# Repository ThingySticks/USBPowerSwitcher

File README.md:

# USB Power Controller

TODO: Write Readme.md

See: https://www.hackster.io/TinamousSteve/alexa-enabled-usb-power-switch-93bab3

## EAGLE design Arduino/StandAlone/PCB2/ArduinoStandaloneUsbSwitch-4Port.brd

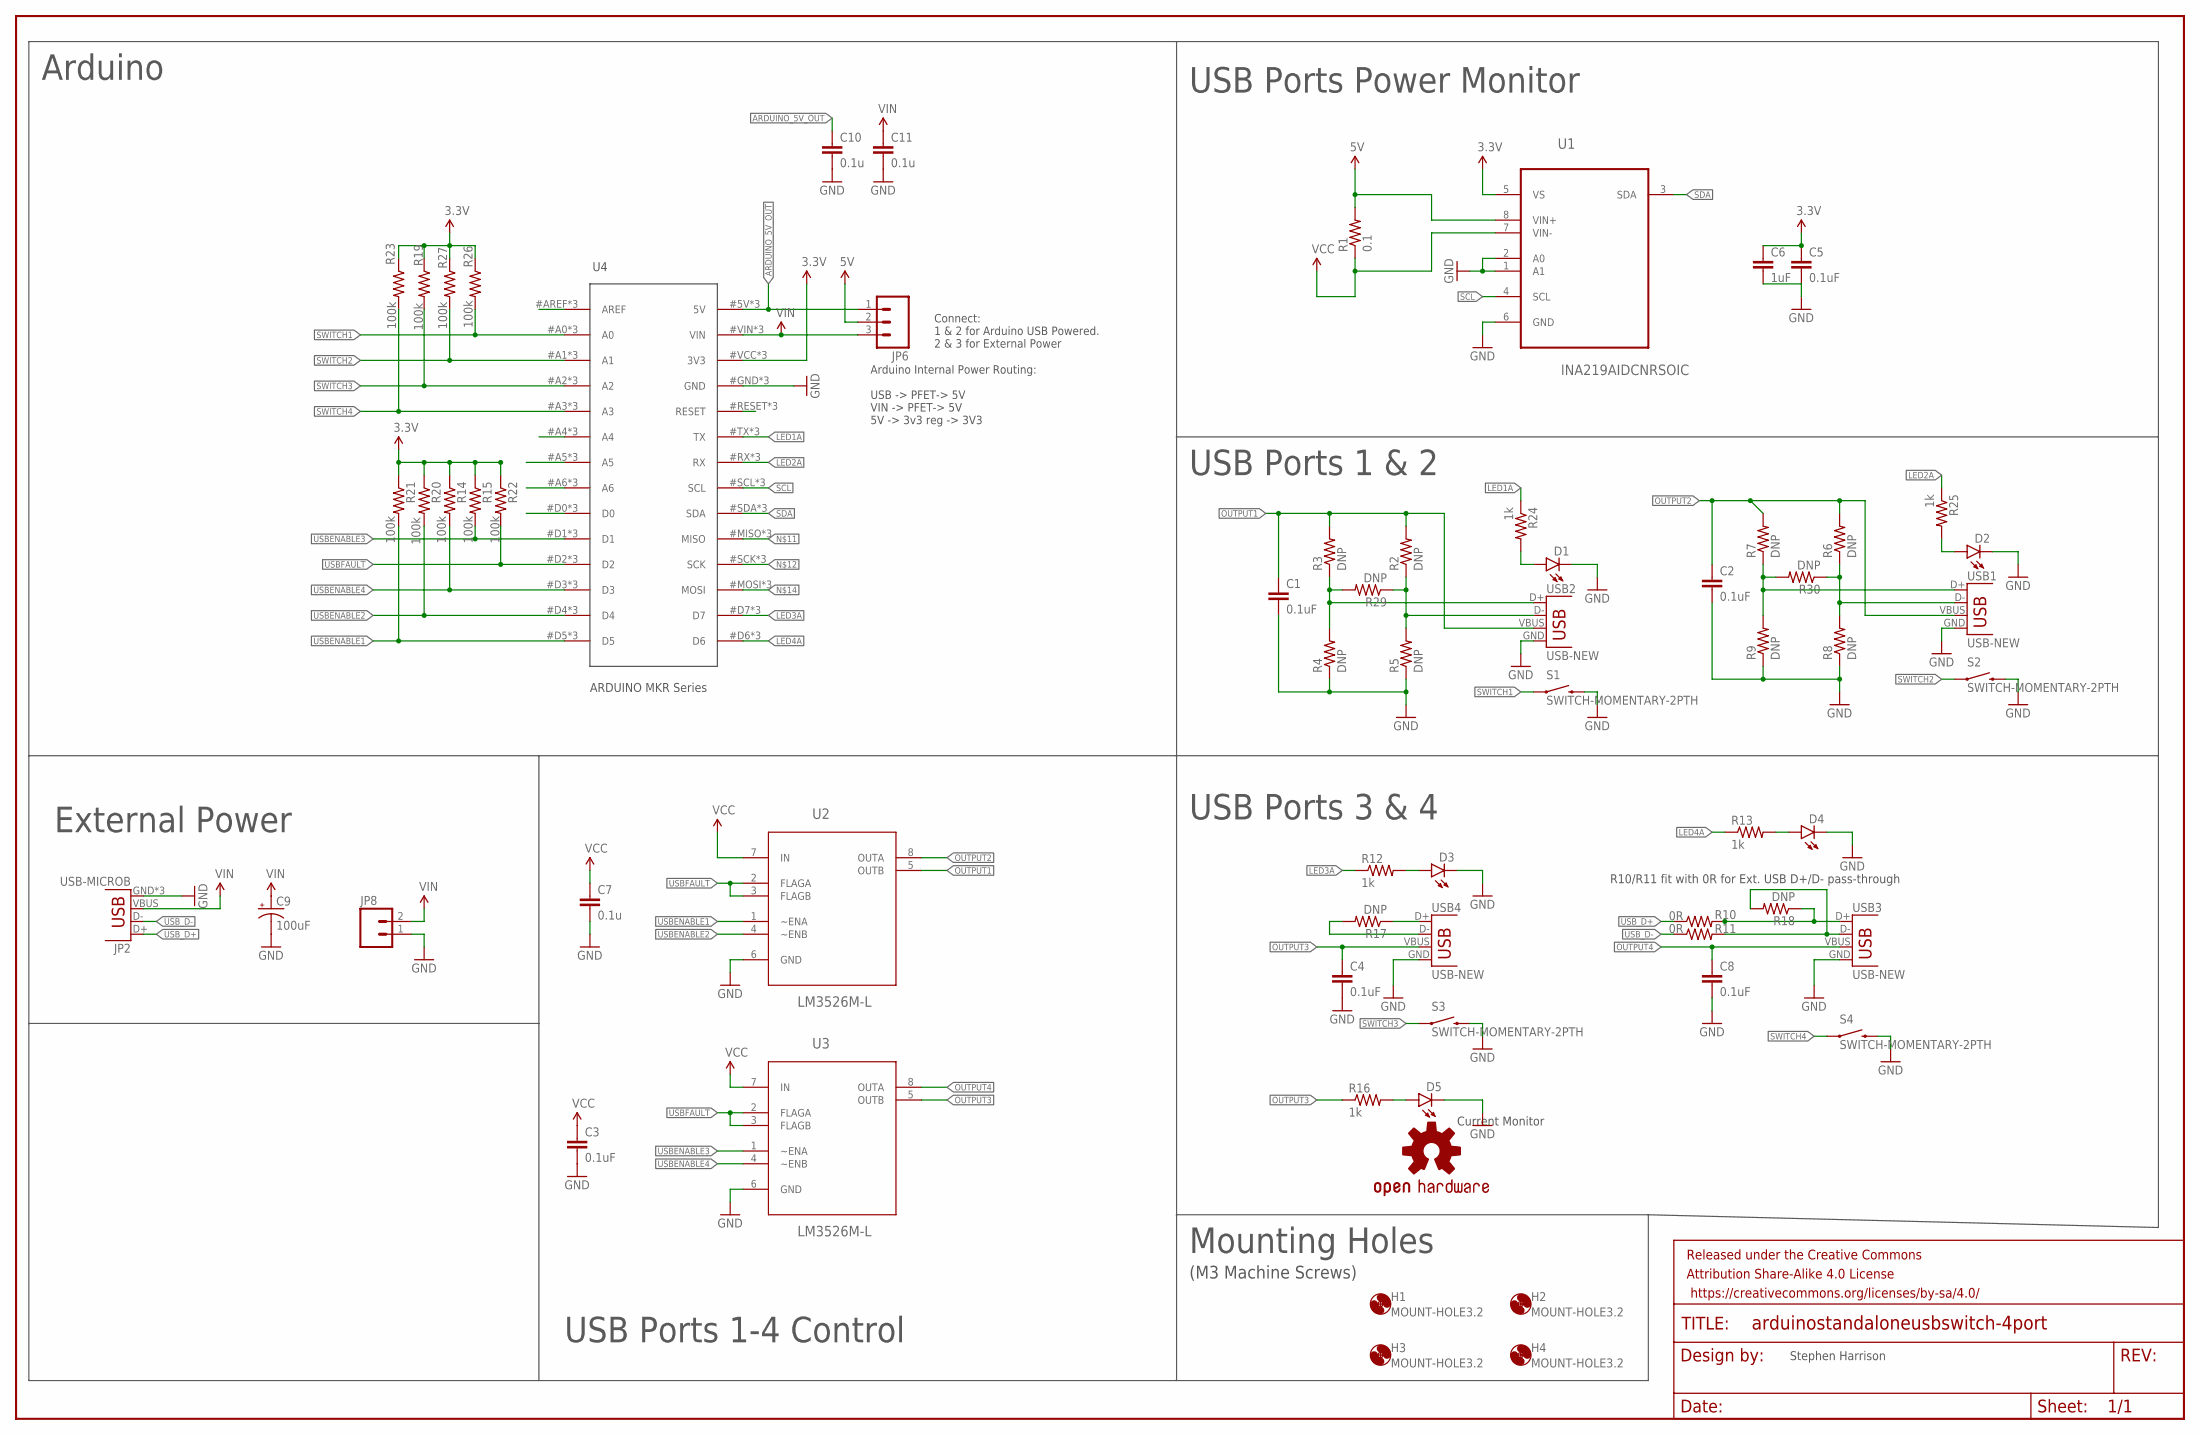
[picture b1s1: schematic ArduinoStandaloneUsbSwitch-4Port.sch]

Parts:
C1, C2, C3, C4, C5, C8: 0.1uF; 0805
C6: 1uF; 0805
C7, C10, C11: 0.1u; 0805
C9: 100uF; EIA7343
D1: LED3MM; FARNELL 1208851
D2, D3, D4: LED3MM
D5: LED1206-BOTTOM; LED-1206-BOTTOM
FRAME1: FRAME-LEDGER; CREATIVE_COMMONS
H1, H2, H3, H4: MOUNT-HOLE3.2; 3,2
JP2: USB-MICROB
JP6: M03PTH; 1X03
JP8: M025MM; SCREWTERMINAL-5MM-2
LOGO1: OSHW-LOGOL; OSHW-LOGO-L
R1: 0.1; 2512; FARNELL 1435952
R2, R3, R4, R5, R6, R7, R8, R9, R17, R18, R29, R30: DNP; 0805
R10, R11: 0R; 0805
R12, R13, R16, R24, R25: 1k; 0805
R14, R15, R19, R20, R21, R22, R23, R26, R27: 100k; 0805
S1: SWITCH-MOMENTARY-2PTH; TACTILE-PTH; FARNELL 2533101
S2, S3, S4: SWITCH-MOMENTARY-2PTH; TACTILE-PTH
U1: INA219AIDCNRSOIC; SO08; FARNELL 2496402
U2, U3: LM3526M-L; SOIC127P640X175-8N
U4: ARDUINO MKR Series; ARDUINO_MKRFOX1200_PROTOPADS
USB1, USB3, USB4: USB-NEW; USB-A-VERTICAL
USB2: USB-NEW; USB-A-VERTICAL; FARNELL 1177882

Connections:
3.3V: C5.1, C6.1, R14.1, R15.1, R19.1, R20.1, R21.1, R22.1, R23.1, R26.1, R27.1, U1.5 (VS), U4.#VCC (3V3), U4.@VCC (3V3), U4.VCC (3V3)
5V: JP6.2, R1.2, U1.8 (VIN+)
ARDUINO_5V_OUT: C10.1, JP6.1, U4.5V, U4.#5V (5V), U4.@5V (5V)
GND: C1.2, C2.2, C3.2, C4.2, C5.2, C6.2, C7.2, C8.2, C9.C (-), C10.2, C11.2, D1.K (C), D2.K (C), D3.K (C), D4.K (C), D5.C, JP2.GND, JP2.MT1 (GND), JP2.MT2 (GND), JP8.1, R4.1, R5.1, R8.1, R9.1, S1.3 (2), S2.3 (2), S3.3 (2), S4.3 (2), U1.1 (A1), U1.2 (A0), U1.6 (GND), U2.6 (GND), U3.6 (GND), U4.#GND (GND), U4.@GND (GND), U4.GND, USB1.GND, USB2.GND, USB3.GND, USB4.GND
LED1A: R24.1, U4.#TX (TX), U4.@TX (TX), U4.TX
LED2A: R25.1, U4.#RX (RX), U4.@RX (RX), U4.RX
LED3A: R12.1, U4.#D7 (D7), U4.@D7 (D7), U4.D7
LED4A: R13.1, U4.#D6 (D6), U4.@D6 (D6), U4.D6
unnamed: R10.2, R18.1, USB3.D+
unnamed: R11.2, R18.2, USB3.D-
unnamed: D1.A, R24.2
unnamed: R17.1, USB4.D+
unnamed: D2.A, R25.2
unnamed: U4.#RESET (RESET), U4.@RESET (RESET), U4.RESET
unnamed: R17.2, USB4.D-
unnamed: R3.1, R4.2, R29.2, USB2.D+
unnamed: U4.#MISO (MISO), U4.@MISO (MISO), U4.MISO
unnamed: U4.#SCK (SCK), U4.@SCK (SCK), U4.SCK
unnamed: R2.1, R5.2, R29.1, USB2.D-
unnamed: U4.#MOSI (MOSI), U4.@MOSI (MOSI), U4.MOSI
unnamed: U4.#A4 (A4), U4.@A4 (A4), U4.A4
unnamed: D3.A, R12.2
unnamed: R6.1, R8.2, R30.1, USB1.D-
unnamed: D4.A, R13.2
unnamed: U4.#AREF (AREF), U4.@AREF (AREF), U4.AREF
unnamed: U4.#D0 (D0), U4.@D0 (D0), U4.D0
unnamed: D5.A, R16.2
unnamed: U4.#A6 (A6), U4.@A6 (A6), U4.A6
unnamed: U4.#A5 (A5), U4.@A5 (A5), U4.A5
OUTPUT1: C1.1, R2.2, R3.2, U2.5 (OUTB), USB2.VBUS
OUTPUT2: C2.1, R6.2, R7.2, U2.8 (OUTA), USB1.VBUS
OUTPUT3: C4.1, R16.1, U3.5 (OUTB), USB4.VBUS
OUTPUT4: C8.1, U3.8 (OUTA), USB3.VBUS
SCL: U1.4 (SCL), U4.#SCL (SCL), U4.@SCL (SCL), U4.SCL
SDA: U1.3 (SDA), U4.#SDA (SDA), U4.@SDA (SDA), U4.SDA
SWITCH1: R26.2, S1.1, U4.#A0 (A0), U4.@A0 (A0), U4.A0
SWITCH2: R27.2, S2.1, U4.#A1 (A1), U4.@A1 (A1), U4.A1
SWITCH3: R19.2, S3.1, U4.#A2 (A2), U4.@A2 (A2), U4.A2
SWITCH4: R23.2, S4.1, U4.#A3 (A3), U4.@A3 (A3), U4.A3
USB2D-: R7.1, R9.2, R30.2, USB1.D+
USBENABLE1: R21.2, U2.1 (~ENA), U4.#D5 (D5), U4.@D5 (D5), U4.D5
USBENABLE2: R20.2, U2.4 (~ENB), U4.#D4 (D4), U4.@D4 (D4), U4.D4
USBENABLE3: R15.2, U3.1 (~ENA), U4.#D1 (D1), U4.@D1 (D1), U4.D1
USBENABLE4: R14.2, U3.4 (~ENB), U4.#D3 (D3), U4.@D3 (D3), U4.D3
USBFAULT: R22.2, U2.2 (FLAGA), U2.3 (FLAGB), U3.2 (FLAGA), U3.3 (FLAGB), U4.#D2 (D2), U4.@D2 (D2), U4.D2
USB_D+: JP2.D+, R10.1
USB_D-: JP2.D-, R11.1
VCC: C3.1, C7.1, R1.1, U1.7 (VIN-), U2.7 (IN), U3.7 (IN)
VIN: C9.A (+), C11.1, JP2.VBUS, JP6.3, JP8.2, U4.#VIN (VIN), U4.@VIN (VIN), U4.VIN

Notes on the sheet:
Arduino Internal Power Routing: USB -> PFET-> 5V VIN -> PFET-> 5V 5V -> 3v3 reg -> 3V3
Connect: 1 & 2 for Arduino USB Powered. 2 & 3 for External Power
Current Monitor
Arduino
USB Ports 1 & 2
USB Ports 3 & 4
USB Ports 1-4 Control
External Power
Mounting Holes
(M3 Machine Screws)
R10/R11 fit with 0R for Ext. USB D+/D- pass-through
USB Ports Power Monitor
Stephen Harrison

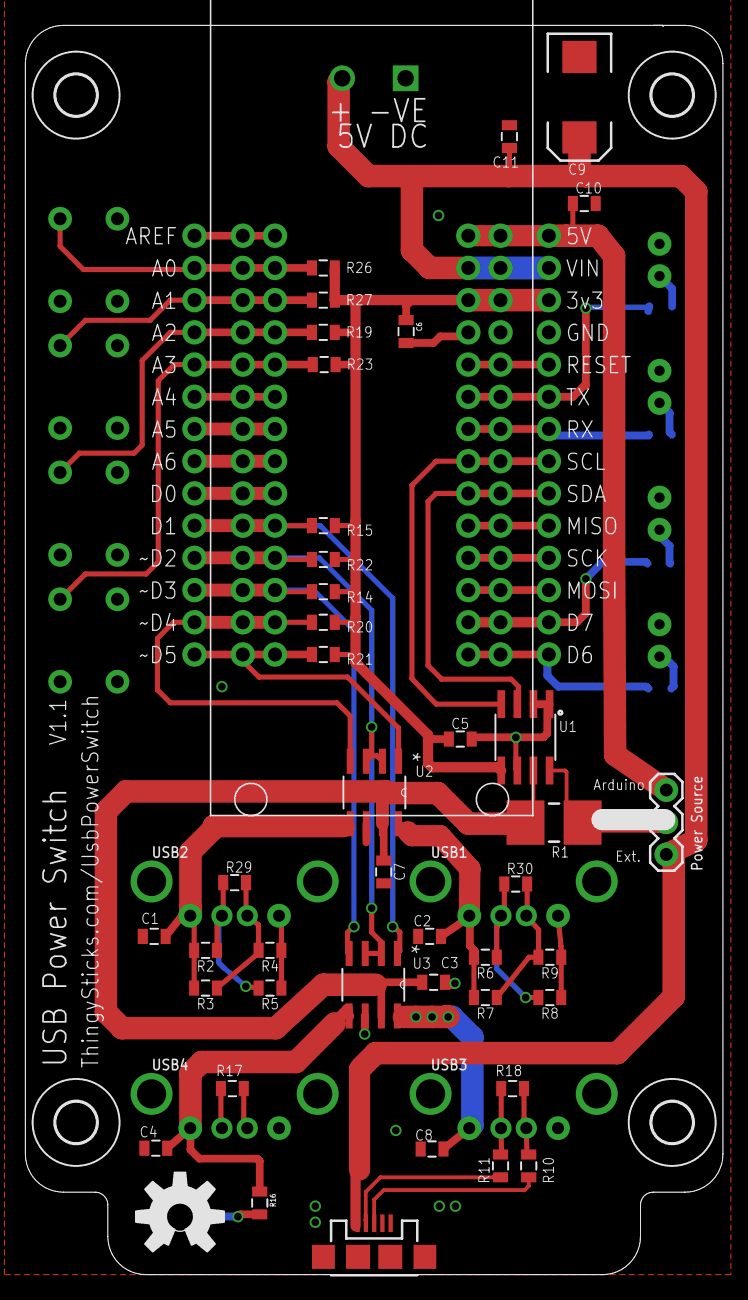
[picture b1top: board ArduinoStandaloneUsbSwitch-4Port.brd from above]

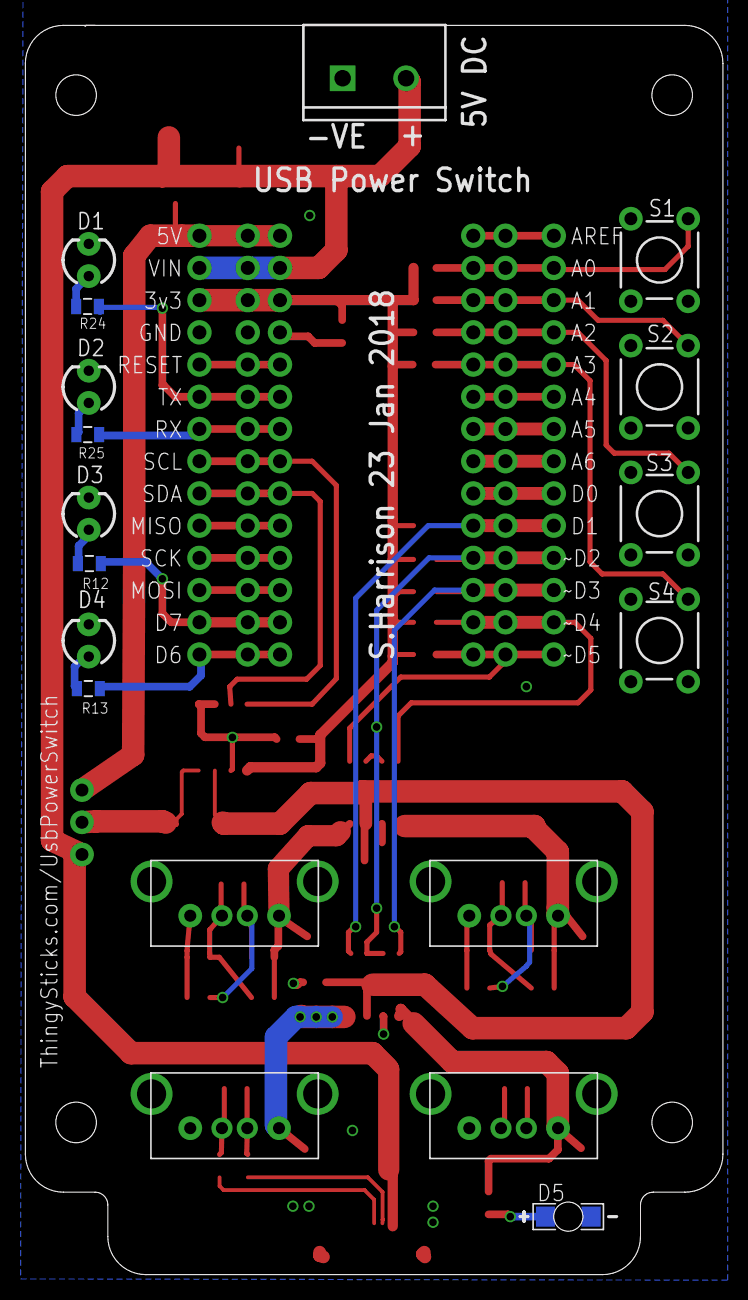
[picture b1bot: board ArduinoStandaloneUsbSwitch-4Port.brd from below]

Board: 2 copper layers, 55.0 x 98.5 mm, 66 parts (14 on the bottom side), 49 nets.

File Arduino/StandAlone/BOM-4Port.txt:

Partlist

Exported from ArduinoStandaloneUsbSwitch-4Port.sch at 11/02/2018 19:11

EAGLE Version 7.4.0 Copyright (c) 1988-2015 CadSoft

Assembly variant: 

Part     Value                       Device                      Package                      Library                    Sheet

C1       0.1uF                       CAP0805                     0805                         SparkFun-Capacitors        1
C2       0.1uF                       CAP0805                     0805                         SparkFun-Capacitors        1
C3       0.1u                        CAP0805                     0805                         SparkFun-Capacitors        1
C4       0.1uF                       CAP0805                     0805                         SparkFun-Capacitors        1
C5                                   CAP0805                     0805                         SparkFun-Capacitors        1
C6                                   CAP0805                     0805                         SparkFun-Capacitors        1
C7       0.1u                        CAP0805                     0805                         SparkFun-Capacitors        1
C8       0.1uF                       CAP0805                     0805                         SparkFun-Capacitors        1
C9       100uF                       100UF-10V-10%(TANT)         EIA7343                      SparkFun-Capacitors        1
C10      0.1u                        CAP0805                     0805                         SparkFun-Capacitors        1
C11      0.1u                        CAP0805                     0805                         SparkFun-Capacitors        1
D1                                   LED3MM                      LED3MM                       SparkFun-LED               1
D2                                   LED3MM                      LED3MM                       SparkFun-LED               1
D3                                   LED3MM                      LED3MM                       SparkFun-LED               1
D4                                   LED3MM                      LED3MM                       SparkFun-LED               1
D5                                   LED1206-BOTTOM              LED-1206-BOTTOM              SparkFun-LED               1
JP2      USB-MICROB                  USB-MICROB                  USB-MICROB                   SparkFun-Connectors        1
JP6                                  M03PTH                      1X03                         SparkFun-Connectors        1
JP8                                  M025MM                      SCREWTERMINAL-5MM-2          SparkFun-Connectors        1
R1       0.1                         0.001OHM-3W-1%(2512)3W/1%   2512                         SparkFun-Resistors         1
R2                                   RESISTOR0805-RES            0805                         SparkFun-Resistors         1
R3                                   RESISTOR0805-RES            0805                         SparkFun-Resistors         1
R4                                   RESISTOR0805-RES            0805                         SparkFun-Resistors         1
R5                                   RESISTOR0805-RES            0805                         SparkFun-Resistors         1
R6                                   RESISTOR0805-RES            0805                         SparkFun-Resistors         1
R7                                   RESISTOR0805-RES            0805                         SparkFun-Resistors         1
R8                                   RESISTOR0805-RES            0805                         SparkFun-Resistors         1
R9                                   RESISTOR0805-RES            0805                         SparkFun-Resistors         1
R10      0R                          RESISTOR0805-RES            0805                         SparkFun-Resistors         1
R11      0R                          RESISTOR0805-RES            0805                         SparkFun-Resistors         1
R12      1k                          RESISTOR0805-RES            0805                         SparkFun-Resistors         1
R13      1k                          RESISTOR0805-RES            0805                         SparkFun-Resistors         1
R14      100k                        RESISTOR0805-RES            0805                         SparkFun-Resistors         1
R15      100k                        RESISTOR0805-RES            0805                         SparkFun-Resistors         1
R16      1k                          RESISTOR0805-RES            0805                         SparkFun-Resistors         1
R17                                  RESISTOR0805-RES            0805                         SparkFun-Resistors         1
R18                                  RESISTOR0805-RES            0805                         SparkFun-Resistors         1
R19      100k                        RESISTOR0805-RES            0805                         SparkFun-Resistors         1
R20      100k                        RESISTOR0805-RES            0805                         SparkFun-Resistors         1
R21      100k                        RESISTOR0805-RES            0805                         SparkFun-Resistors         1
R22      100k                        RESISTOR0805-RES            0805                         SparkFun-Resistors         1
R23      100k                        RESISTOR0805-RES            0805                         SparkFun-Resistors         1
R24      1k                          RESISTOR0805-RES            0805                         SparkFun-Resistors         1
R25      1k                          RESISTOR0805-RES            0805                         SparkFun-Resistors         1
R26      100k                        RESISTOR0805-RES            0805                         SparkFun-Resistors         1
R27      100k                        RESISTOR0805-RES            0805                         SparkFun-Resistors         1
R29                                  RESISTOR0805-RES            0805                         SparkFun-Resistors         1
R30                                  RESISTOR0805-RES            0805                         SparkFun-Resistors         1
S1       SWITCH-MOMENTARY-2PTH       SWITCH-MOMENTARY-2PTH       TACTILE-PTH                  SparkFun-Electromechanical 1
S2       SWITCH-MOMENTARY-2PTH       SWITCH-MOMENTARY-2PTH       TACTILE-PTH                  SparkFun-Electromechanical 1
S3       SWITCH-MOMENTARY-2PTH       SWITCH-MOMENTARY-2PTH       TACTILE-PTH                  SparkFun-Electromechanical 1
S4       SWITCH-MOMENTARY-2PTH       SWITCH-MOMENTARY-2PTH       TACTILE-PTH                  SparkFun-Electromechanical 1
U1       INA219AIDCNRSOIC            INA219AIDCNRSOIC            SO08                         INA219AIDCNR               1
U2       LM3526M-L                   LM3526M-L                   SOIC127P640X175-8N           LM3256M-L                  1
U3       LM3526M-L                   LM3526M-L                   SOIC127P640X175-8N           LM3256M-L                  1
U4       ARDUINO_MKRFOX1200PROTOPADS ARDUINO_MKRFOX1200PROTOPADS ARDUINO_MKRFOX1200_PROTOPADS Arduino                    1
USB1     USB-NEW                     USB-NEW                     USB-A-VERTICAL               Tinamous                   1
USB2     USB-NEW                     USB-NEW                     USB-A-VERTICAL               Tinamous                   1
USB3     USB-NEW                     USB-NEW                     USB-A-VERTICAL               Tinamous                   1
USB4     USB-NEW                     USB-NEW                     USB-A-VERTICAL               Tinamous                   1

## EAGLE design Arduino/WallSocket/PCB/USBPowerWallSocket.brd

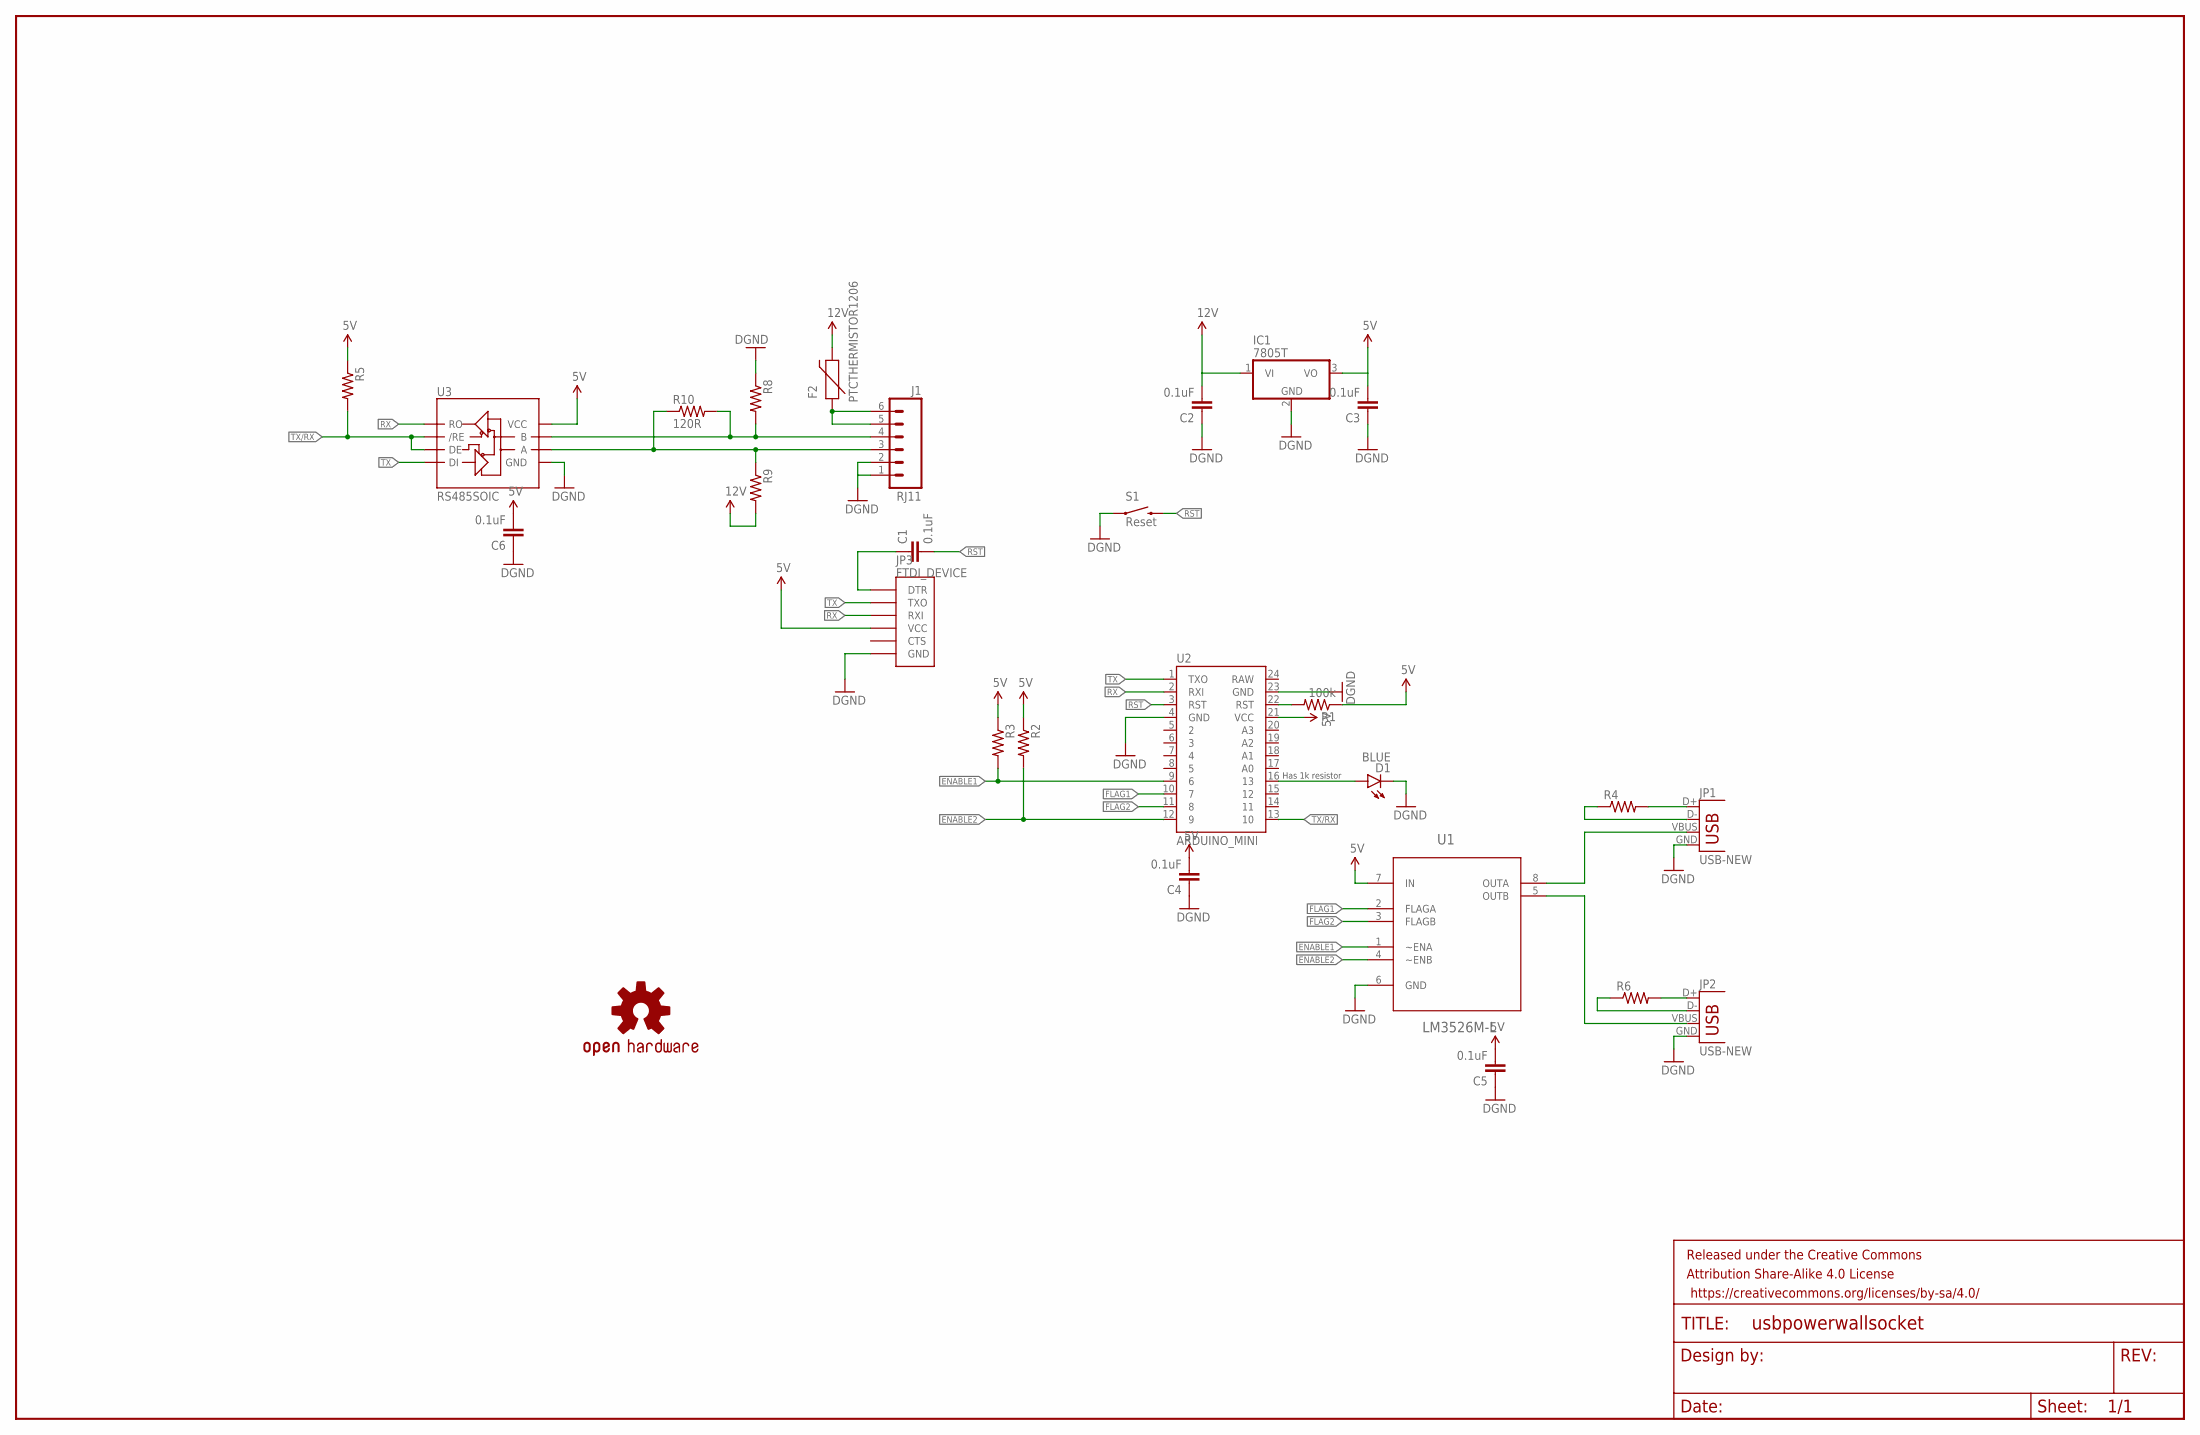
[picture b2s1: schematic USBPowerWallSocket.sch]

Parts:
C1, C2, C3, C4, C5, C6: 0.1uF; 0805
D1: BLUE; LED-1206
F2: PTCTHERMISTOR1206; PTC-1206
FRAME1: FRAME-LEDGER; CREATIVE_COMMONS
IC1: 7805T; TO220H
J1: RJ11; RJ11-6
JP1, JP2: USB-NEW; USB-A-VERTICAL
JP3: FTDI_DEVICE; FTDI_DEVICE_SIDE
LOGO1: OSHW-LOGOM; OSHW-LOGO-M
R1: 100k; 0805
R2, R3, R4, R5, R6, R8, R9: RESISTOR0805-RES; 0805
R10: 120R; 0805
S1: Reset; TACTILE-PTH
U1: LM3526M-L; SOIC127P640X175-8N
U2: ARDUINO_MINI
U3: RS485SOIC; SO08

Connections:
5V: C3.2, C4.2, C5.2, C6.2, IC1.3 (VO), JP3.P$4 (VCC), R1.1, R2.1, R3.1, R5.1, U1.7 (IN), U2.21 (VCC), U3.8 (VCC)
12V: C2.2, F2.2, IC1.1 (VI), R9.2
A: J1.3, R9.1, R10.1, U3.6 (A)
B: J1.4, R8.2, R10.2, U3.7 (B)
ENABLE1: R3.2, U1.1 (~ENA), U2.9 (6)
ENABLE2: R2.2, U1.4 (~ENB), U2.12 (9)
FLAG1: U1.2 (FLAGA), U2.10 (7)
FLAG2: U1.3 (FLAGB), U2.11 (8)
GND: C2.1, C3.1, C4.1, C5.1, C6.1, D1.C, IC1.2 (GND), J1.1, J1.2, JP1.GND, JP2.GND, JP3.P$6 (GND), R8.1, S1.1, U1.6 (GND), U2.4 (GND), U2.23 (GND), U3.5 (GND)
unnamed: JP2.D-, R6.1
unnamed: D1.A, U2.16 (13)
unnamed: JP2.D+, R6.2
unnamed: JP1.D-, R4.1
unnamed: JP1.D+, R4.2
unnamed: F2.1, J1.5, J1.6
unnamed: JP1.VBUS, U1.8 (OUTA)
unnamed: JP2.VBUS, U1.5 (OUTB)
unnamed: C1.1, JP3.P$1 (DTR)
RST: C1.2, S1.3 (2), U2.3 (RST)
RST2: R1.2, U2.22 (RST)
RX: JP3.P$3 (RXI), U2.2 (RXI), U3.1 (RO)
TX: JP3.P$2 (TXO), U2.1 (TXO), U3.4 (DI)
TX/RX: R5.2, U2.13 (10), U3.2 (/RE), U3.3 (DE)

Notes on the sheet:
Has 1k resistor

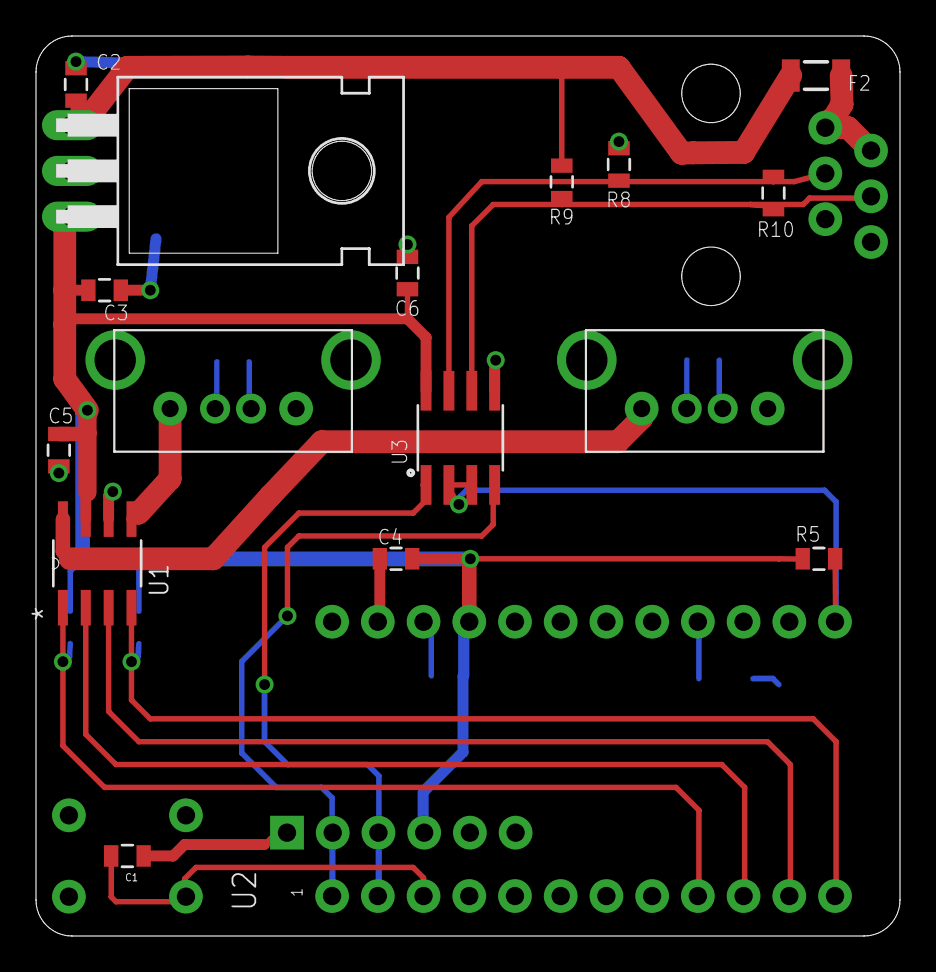
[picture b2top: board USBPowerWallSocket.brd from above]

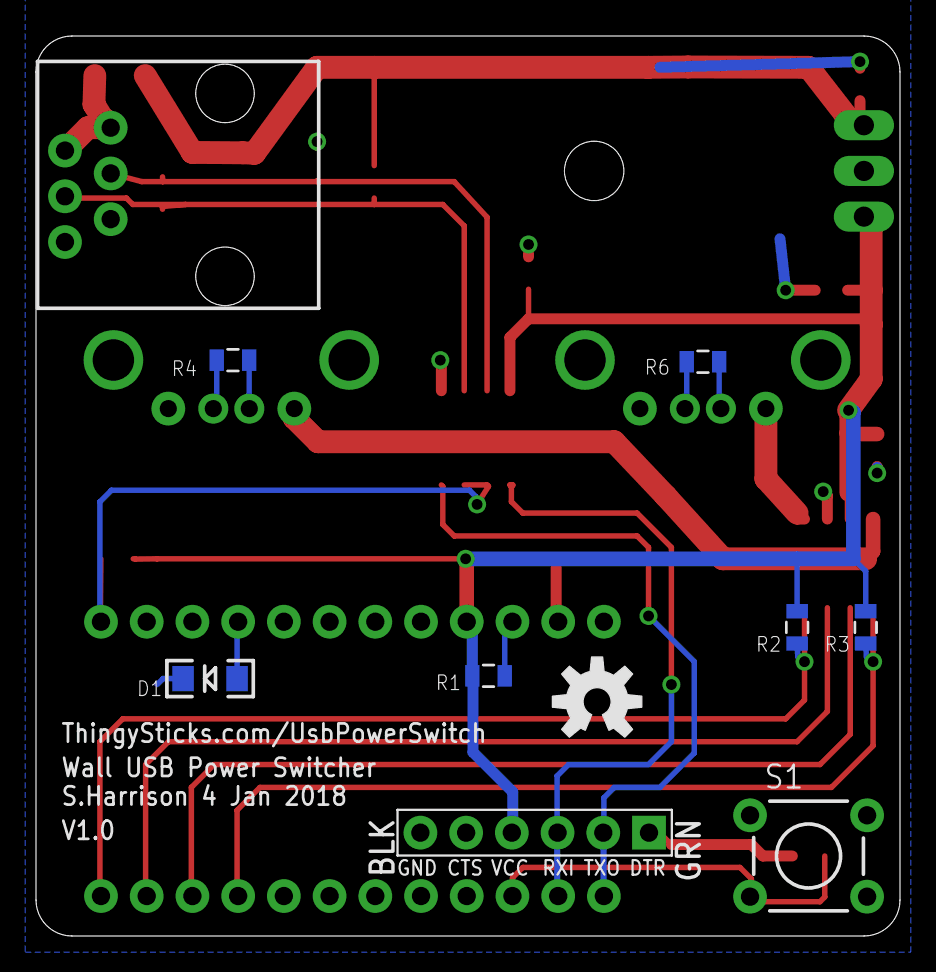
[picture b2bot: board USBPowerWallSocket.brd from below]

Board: 2 copper layers, 48.0 x 50.0 mm, 28 parts (10 on the bottom side), 23 nets.

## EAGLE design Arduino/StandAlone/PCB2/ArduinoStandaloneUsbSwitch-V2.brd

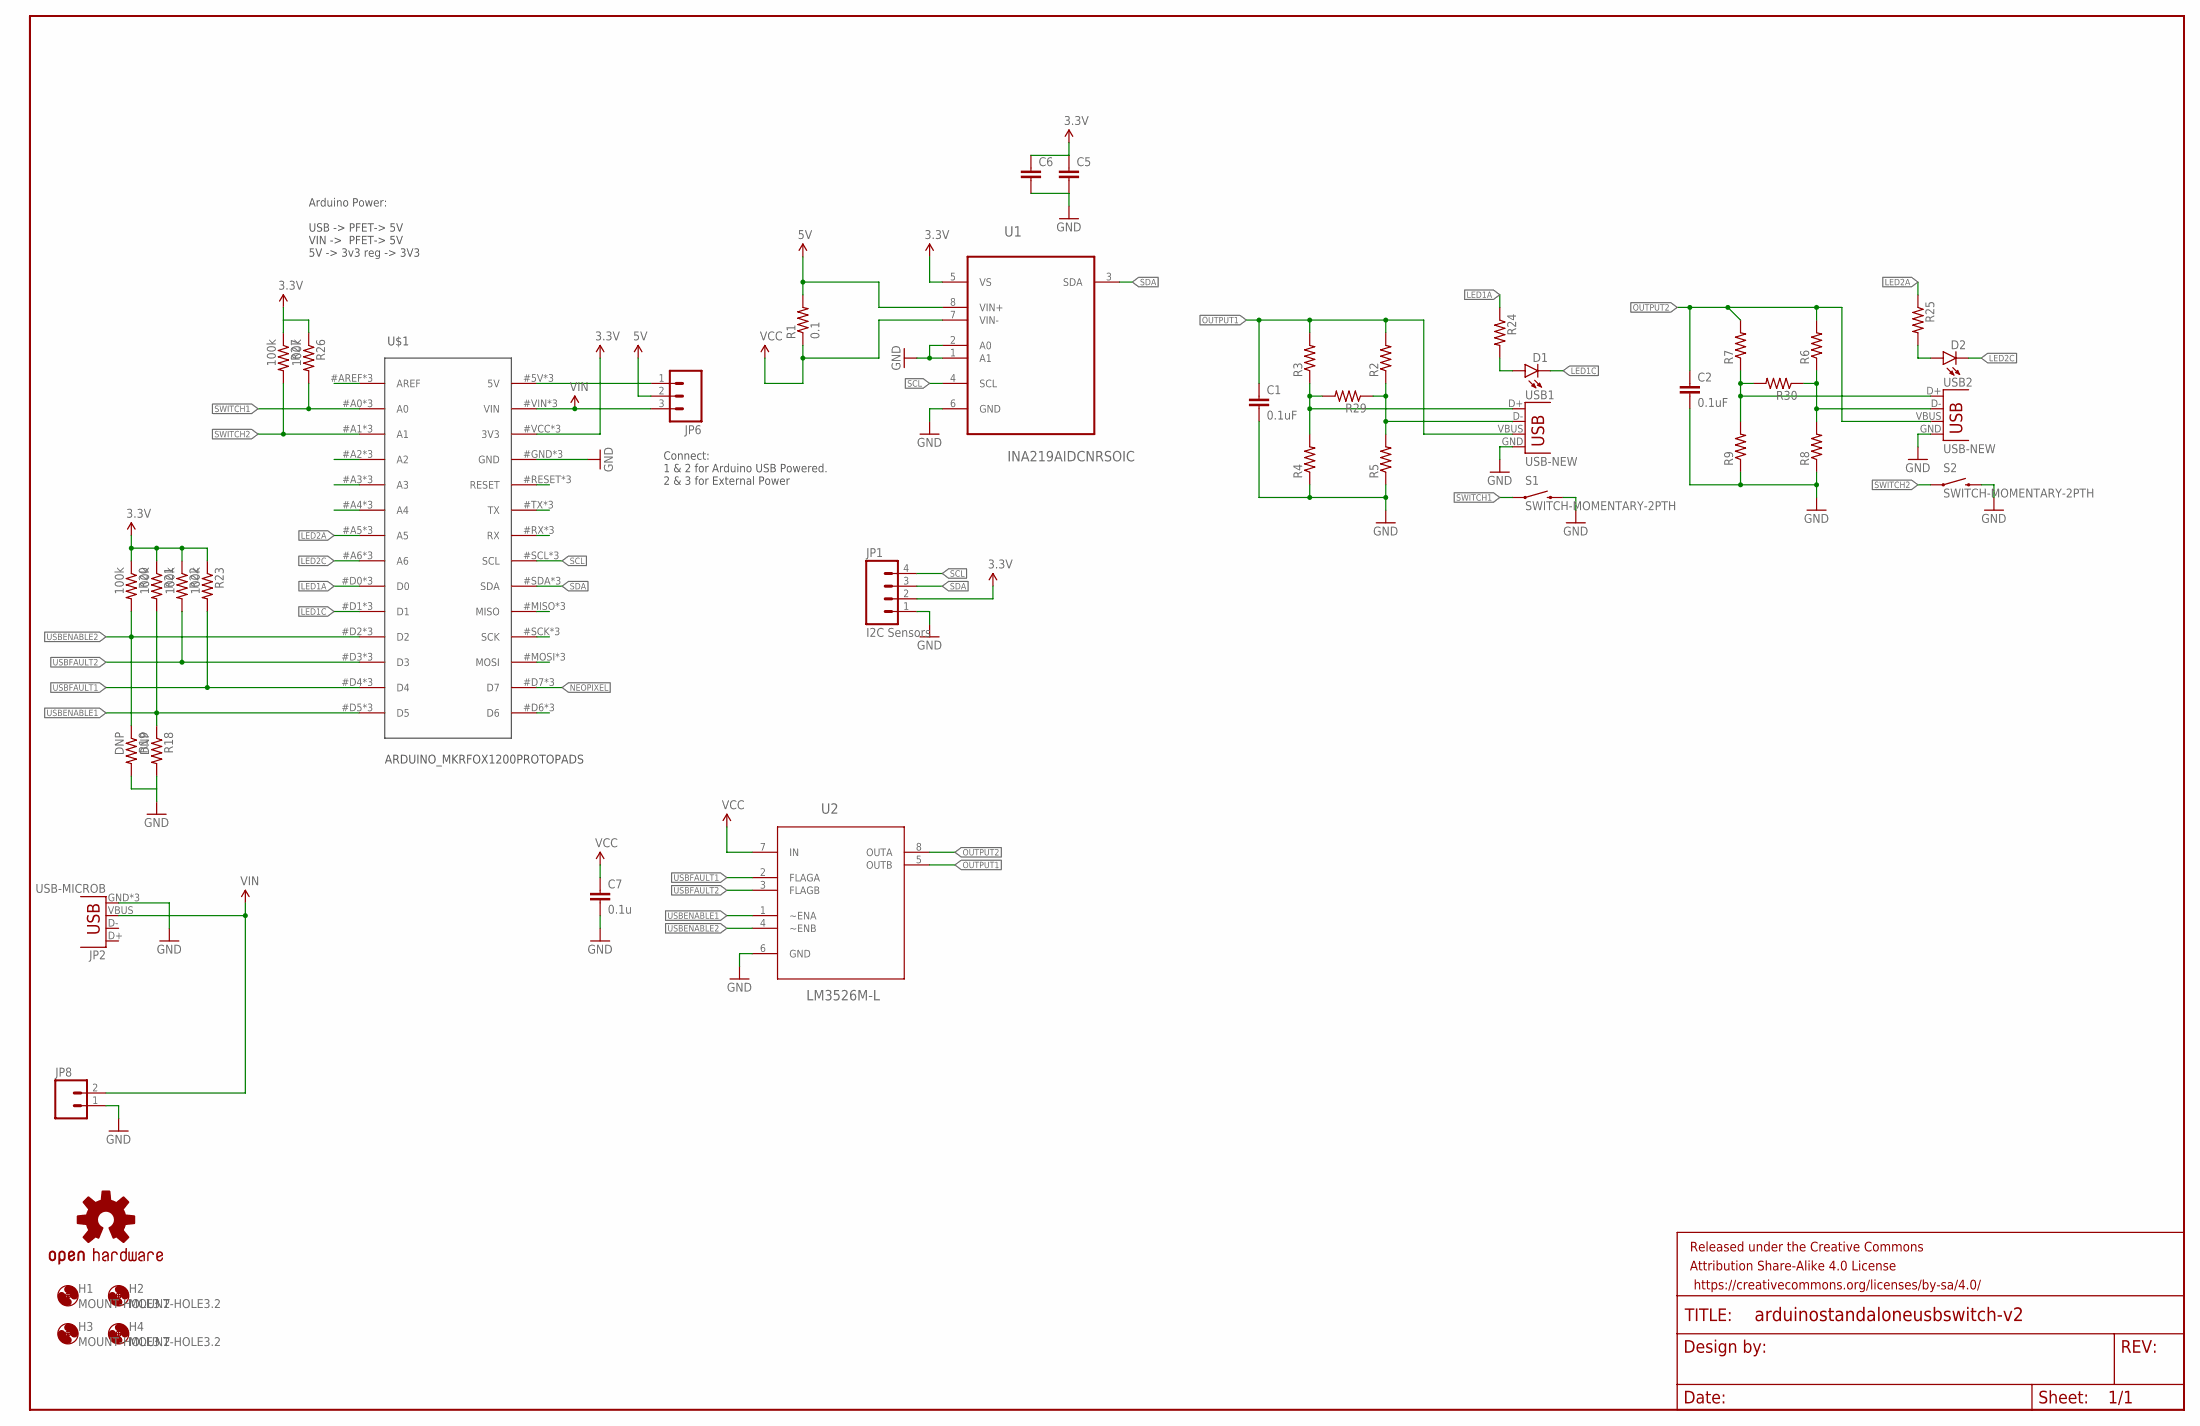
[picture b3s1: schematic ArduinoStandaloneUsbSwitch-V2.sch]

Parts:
C1, C2: 0.1uF; 0805
C5, C6: CAP0805; 0805
C7: 0.1u; 0805
D1, D2: LED3MM
FRAME1: FRAME-LEDGER; CREATIVE_COMMONS
H1, H2, H3, H4: MOUNT-HOLE3.2; 3,2
JP1: I2C Sensors; MOLEX-1X4
JP2: USB-MICROB
JP6: M03PTH; 1X03
JP8: M025MM; SCREWTERMINAL-5MM-2
LOGO1: OSHW-LOGOM; OSHW-LOGO-M
R1: 0.1; 2512
R2, R3, R4, R5, R6, R7, R8, R9, R24, R25, R29, R30: RESISTOR0805-RES; 0805
R18, R19: DNP; 0805
R20, R21, R22, R23, R26, R27: 100k; 0805
S1, S2: SWITCH-MOMENTARY-2PTH; TACTILE-PTH
U1: INA219AIDCNRSOIC; SO08
U2: LM3526M-L; SOIC127P640X175-8N
U$1: ARDUINO_MKRFOX1200PROTOPADS; ARDUINO_MKRFOX1200_PROTOPADS
USB1, USB2: USB-NEW; USB-A-VERTICAL

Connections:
3.3V: C5.1, C6.1, JP1.2, R20.1, R21.1, R22.1, R23.1, R26.1, R27.1, U1.5 (VS), U$1.#VCC (3V3), U$1.@VCC (3V3), U$1.VCC (3V3)
5V: JP6.2, R1.2, U1.8 (VIN+)
GND: C1.2, C2.2, C5.2, C6.2, C7.2, JP1.1, JP2.GND, JP2.MT1 (GND), JP2.MT2 (GND), JP8.1, R4.1, R5.1, R8.1, R9.1, R18.2, R19.2, S1.3 (2), S2.3 (2), U1.1 (A1), U1.2 (A0), U1.6 (GND), U2.6 (GND), U$1.#GND (GND), U$1.@GND (GND), U$1.GND, USB1.GND, USB2.GND
LED1A: R24.1, U$1.#D0 (D0), U$1.@D0 (D0), U$1.D0
LED1C: D1.K (C), U$1.#D1 (D1), U$1.@D1 (D1), U$1.D1
LED2A: R25.1, U$1.#A5 (A5), U$1.@A5 (A5), U$1.A5
LED2C: D2.K (C), U$1.#A6 (A6), U$1.@A6 (A6), U$1.A6
unnamed: JP6.1, U$1.5V, U$1.#5V (5V), U$1.@5V (5V)
unnamed: D1.A, R24.2
unnamed: D2.A, R25.2
unnamed: U$1.#RESET (RESET), U$1.@RESET (RESET), U$1.RESET
unnamed: U$1.#TX (TX), U$1.@TX (TX), U$1.TX
unnamed: U$1.#RX (RX), U$1.@RX (RX), U$1.RX
unnamed: R3.1, R4.2, R29.2, USB1.D+
unnamed: U$1.#MISO (MISO), U$1.@MISO (MISO), U$1.MISO
unnamed: U$1.#SCK (SCK), U$1.@SCK (SCK), U$1.SCK
unnamed: R2.1, R5.2, R29.1, USB1.D-
unnamed: U$1.#MOSI (MOSI), U$1.@MOSI (MOSI), U$1.MOSI
unnamed: U$1.#D6 (D6), U$1.@D6 (D6), U$1.D6
unnamed: U$1.#A4 (A4), U$1.@A4 (A4), U$1.A4
unnamed: U$1.#A3 (A3), U$1.@A3 (A3), U$1.A3
unnamed: R6.1, R8.2, R30.1, USB2.D-
unnamed: U$1.#A2 (A2), U$1.@A2 (A2), U$1.A2
unnamed: U$1.#AREF (AREF), U$1.@AREF (AREF), U$1.AREF
NEOPIXEL: U$1.#D7 (D7), U$1.@D7 (D7), U$1.D7
OUTPUT1: C1.1, R2.2, R3.2, U2.5 (OUTB), USB1.VBUS
OUTPUT2: C2.1, R6.2, R7.2, U2.8 (OUTA), USB2.VBUS
SCL: JP1.4, U1.4 (SCL), U$1.#SCL (SCL), U$1.@SCL (SCL), U$1.SCL
SDA: JP1.3, U1.3 (SDA), U$1.#SDA (SDA), U$1.@SDA (SDA), U$1.SDA
SWITCH1: R26.2, S1.1, U$1.#A0 (A0), U$1.@A0 (A0), U$1.A0
SWITCH2: R27.2, S2.1, U$1.#A1 (A1), U$1.@A1 (A1), U$1.A1
USB2D-: R7.1, R9.2, R30.2, USB2.D+
USBENABLE1: R18.1, R21.2, U2.1 (~ENA), U$1.#D5 (D5), U$1.@D5 (D5), U$1.D5
USBENABLE2: R19.1, R20.2, U2.4 (~ENB), U$1.#D2 (D2), U$1.@D2 (D2), U$1.D2
USBFAULT1: R23.2, U2.2 (FLAGA), U$1.#D4 (D4), U$1.@D4 (D4), U$1.D4
USBFAULT2: R22.2, U2.3 (FLAGB), U$1.#D3 (D3), U$1.@D3 (D3), U$1.D3
VCC: C7.1, R1.1, U1.7 (VIN-), U2.7 (IN)
VIN: JP2.VBUS, JP6.3, JP8.2, U$1.#VIN (VIN), U$1.@VIN (VIN), U$1.VIN

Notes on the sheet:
Arduino Power: USB -> PFET-> 5V VIN -> PFET-> 5V 5V -> 3v3 reg -> 3V3
Connect: 1 & 2 for Arduino USB Powered. 2 & 3 for External Power

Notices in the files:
parts and their libraries:
SparkFun-Capacitors: Licensing: Creative Commons ShareAlike 4.0 International - https://creativecommons.org/licenses/by-sa/4.0
SparkFun-Aesthetics: Released under the Creative Commons Attribution Share-Alike 4.0 License
SparkFun-Aesthetics: https://creativecommons.org/licenses/by-sa/4.0
